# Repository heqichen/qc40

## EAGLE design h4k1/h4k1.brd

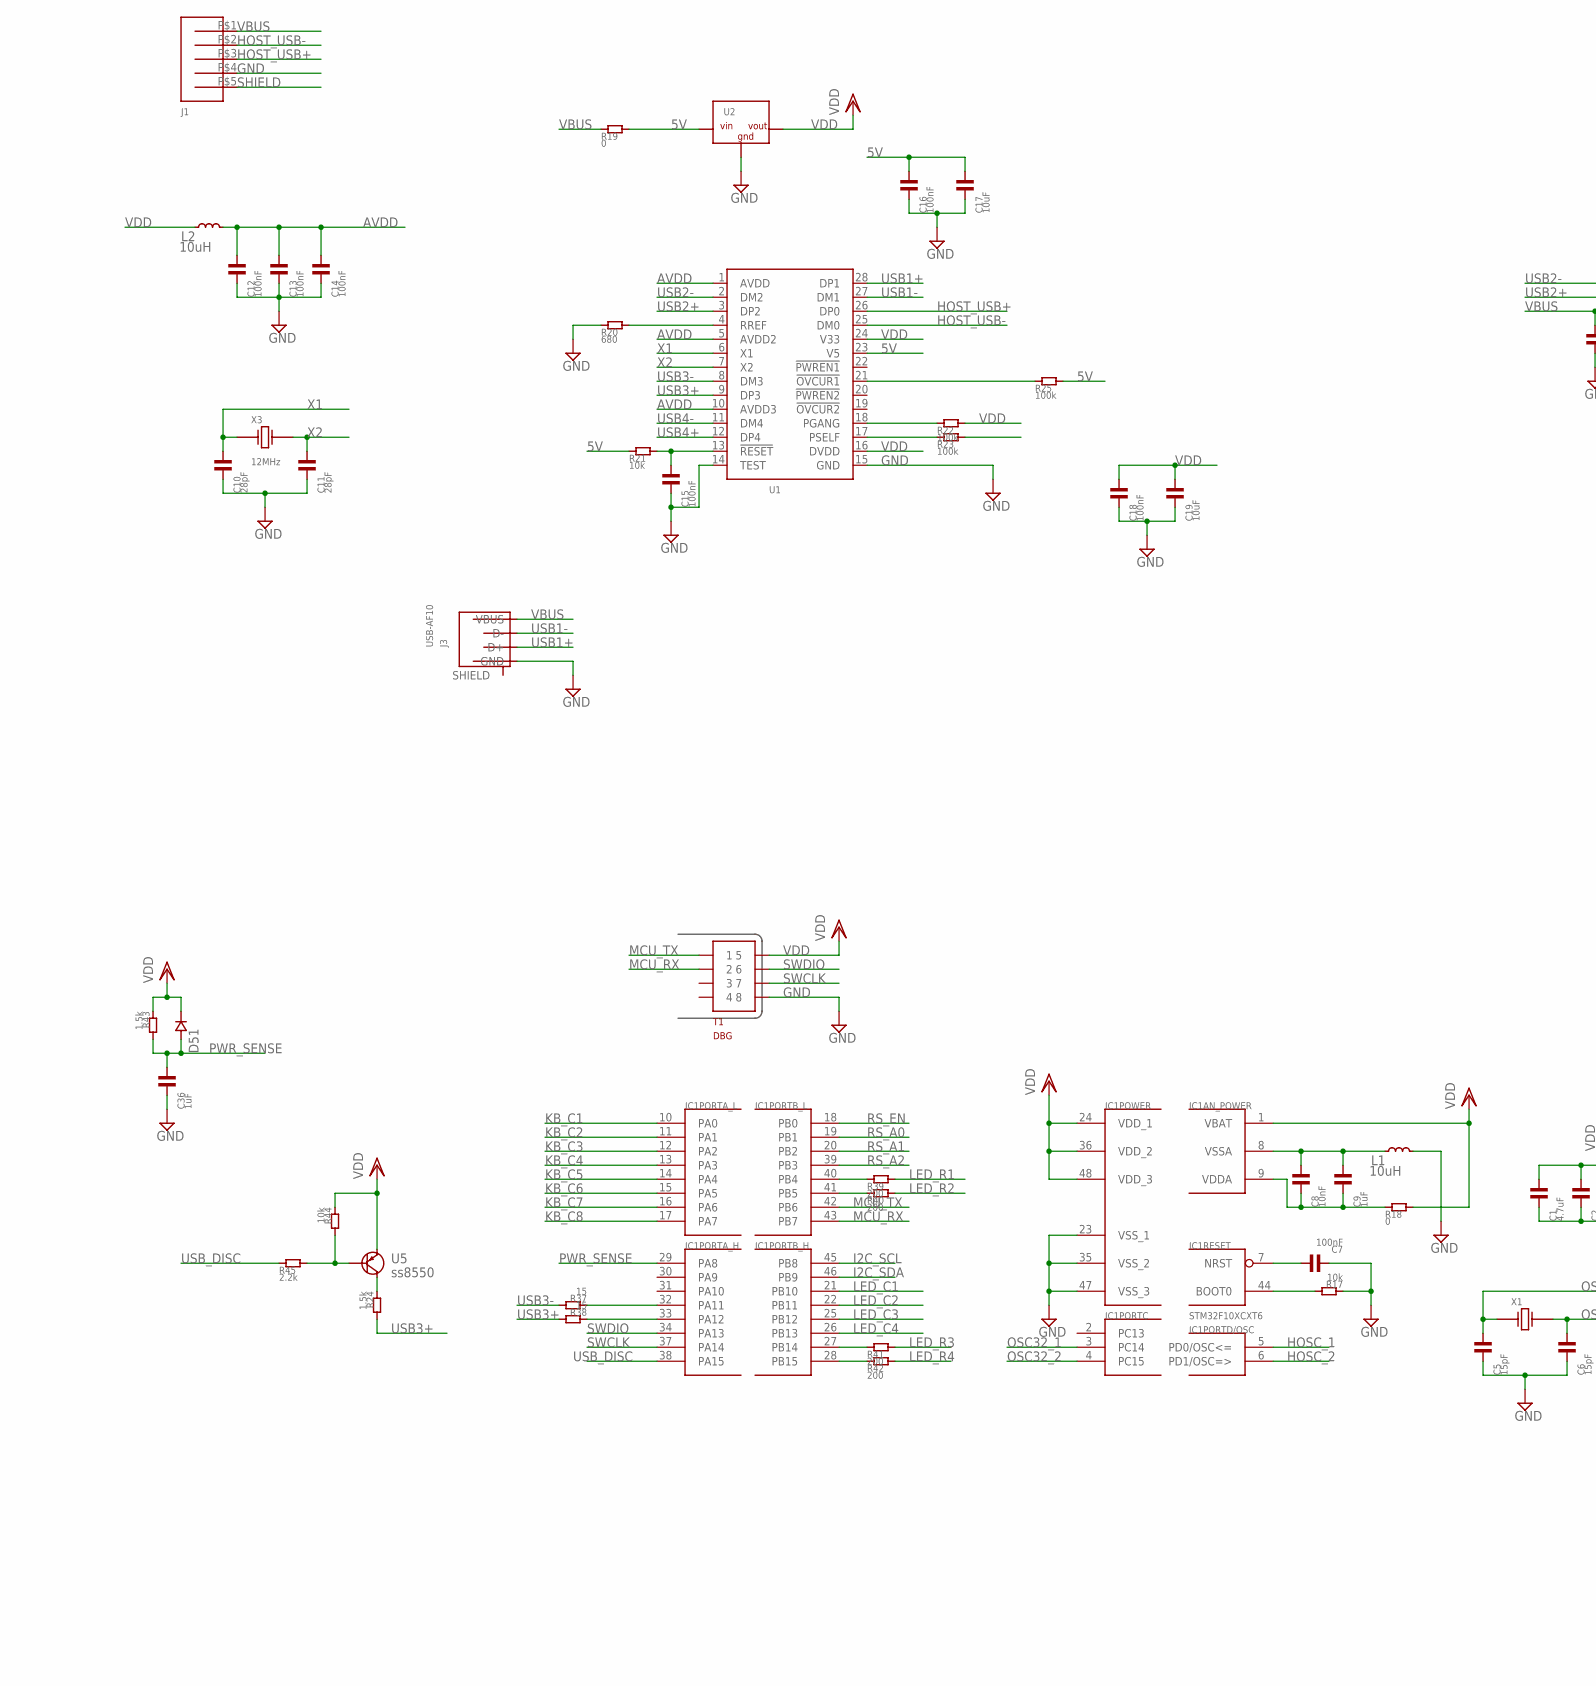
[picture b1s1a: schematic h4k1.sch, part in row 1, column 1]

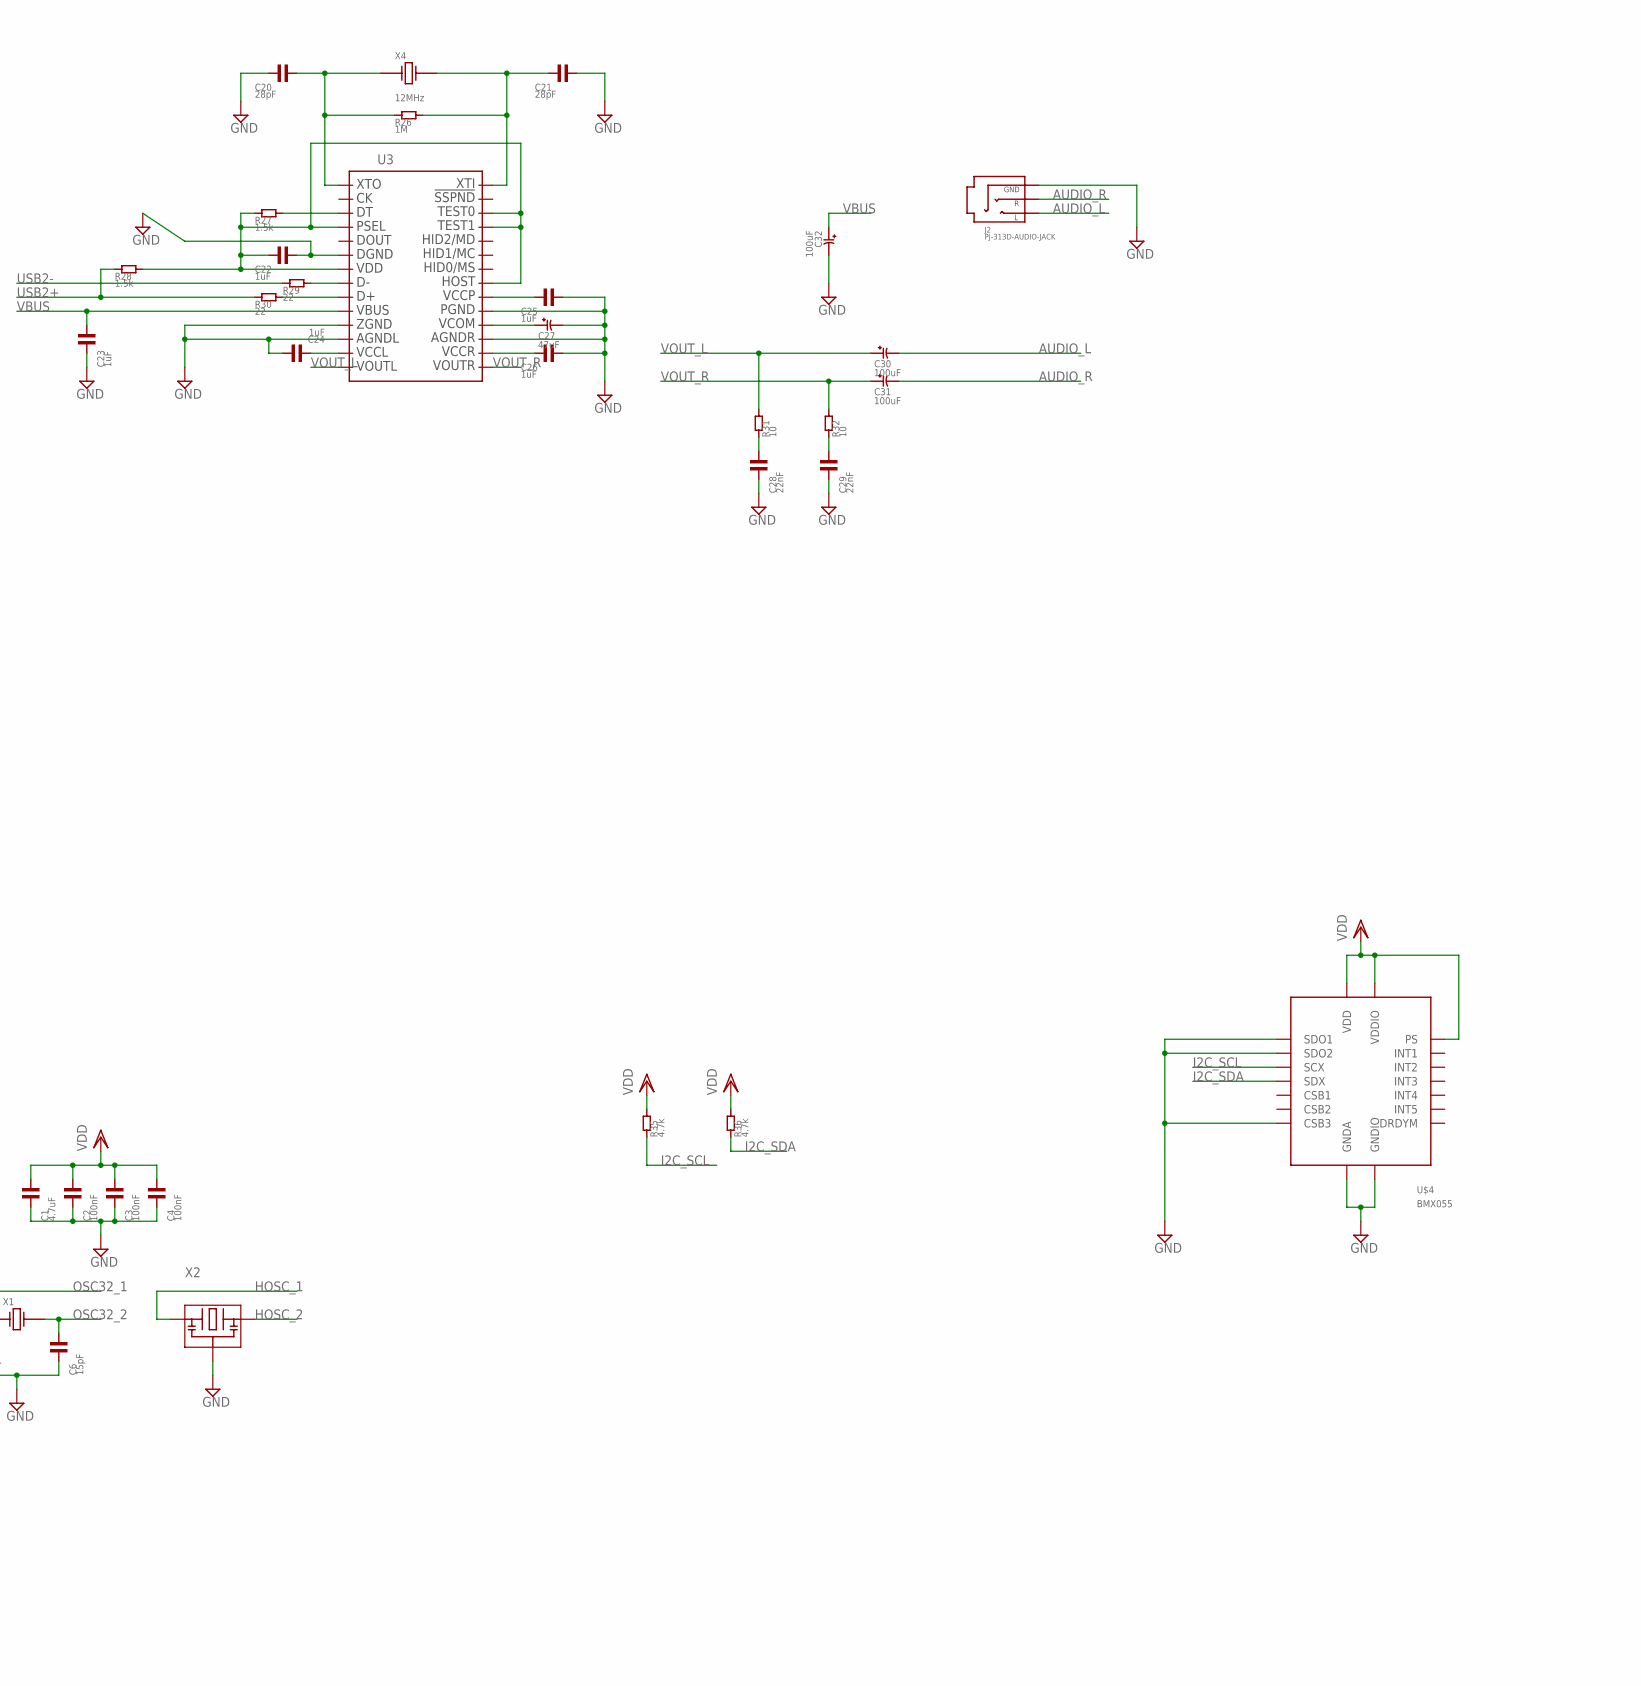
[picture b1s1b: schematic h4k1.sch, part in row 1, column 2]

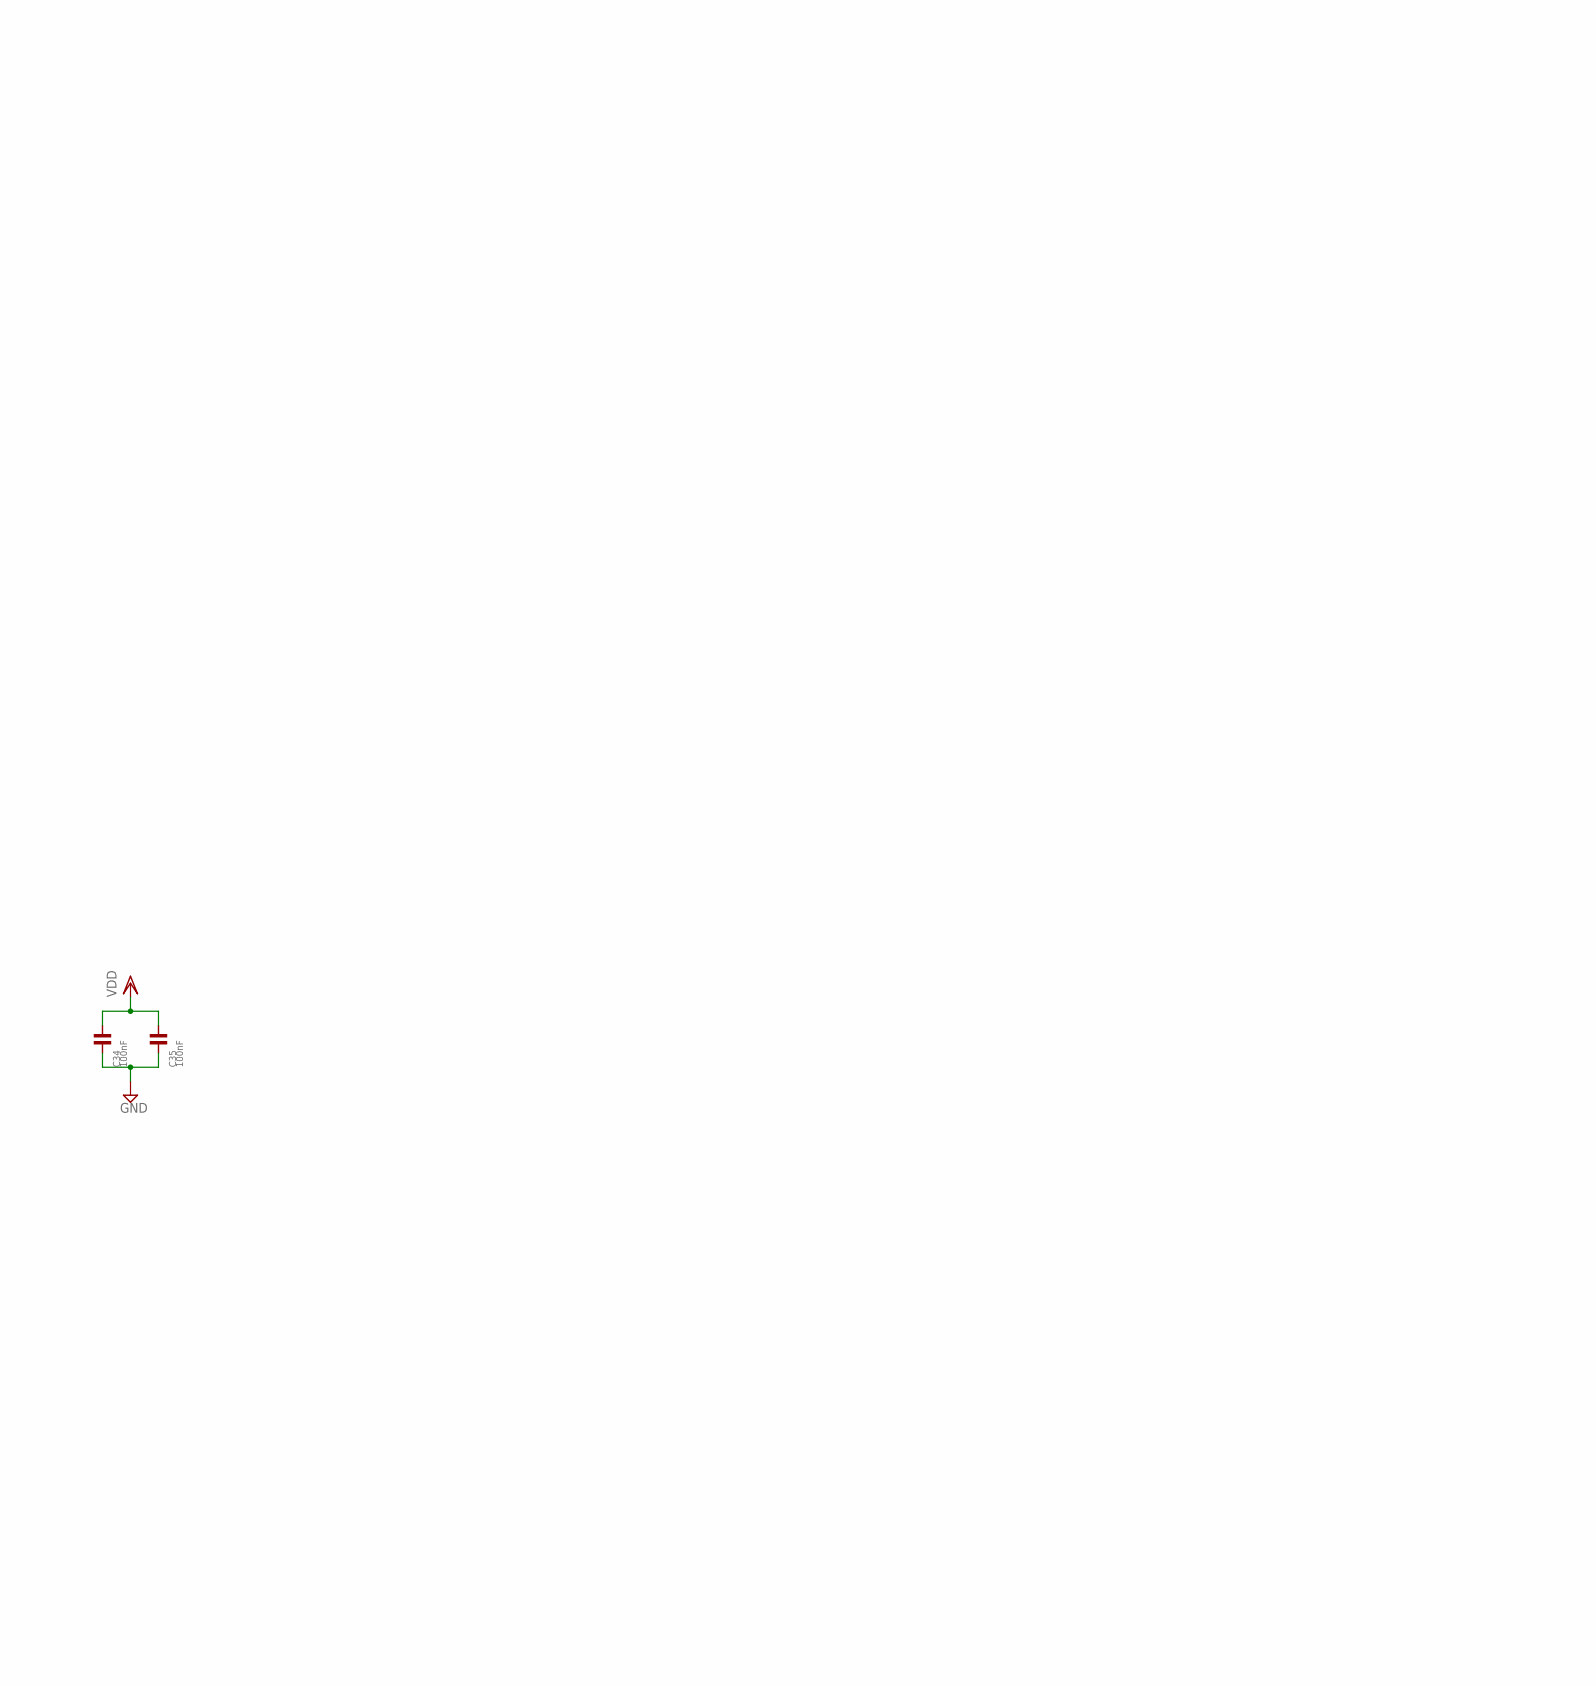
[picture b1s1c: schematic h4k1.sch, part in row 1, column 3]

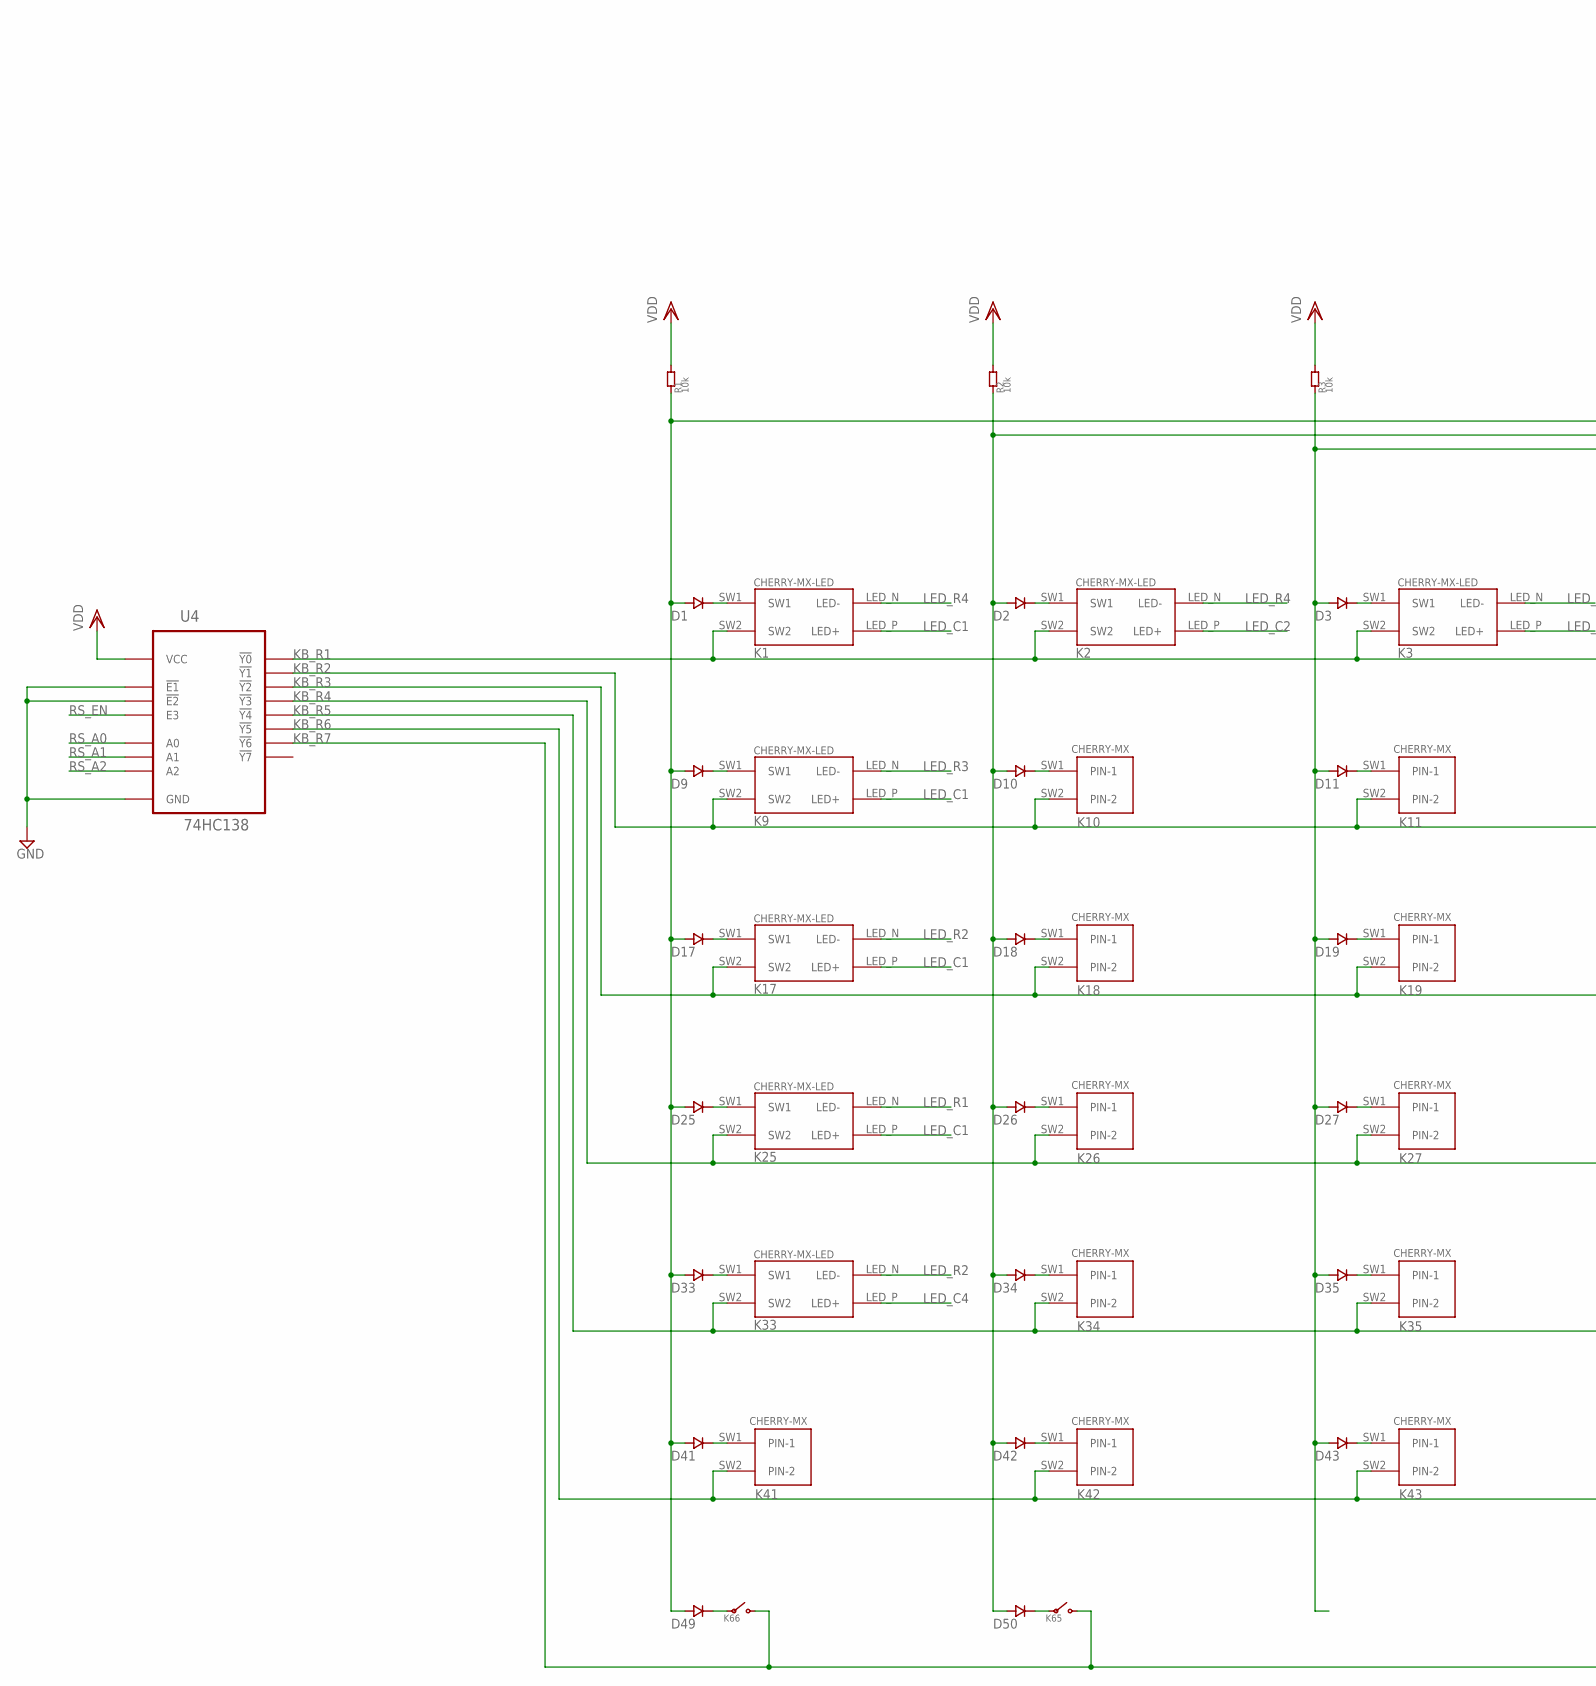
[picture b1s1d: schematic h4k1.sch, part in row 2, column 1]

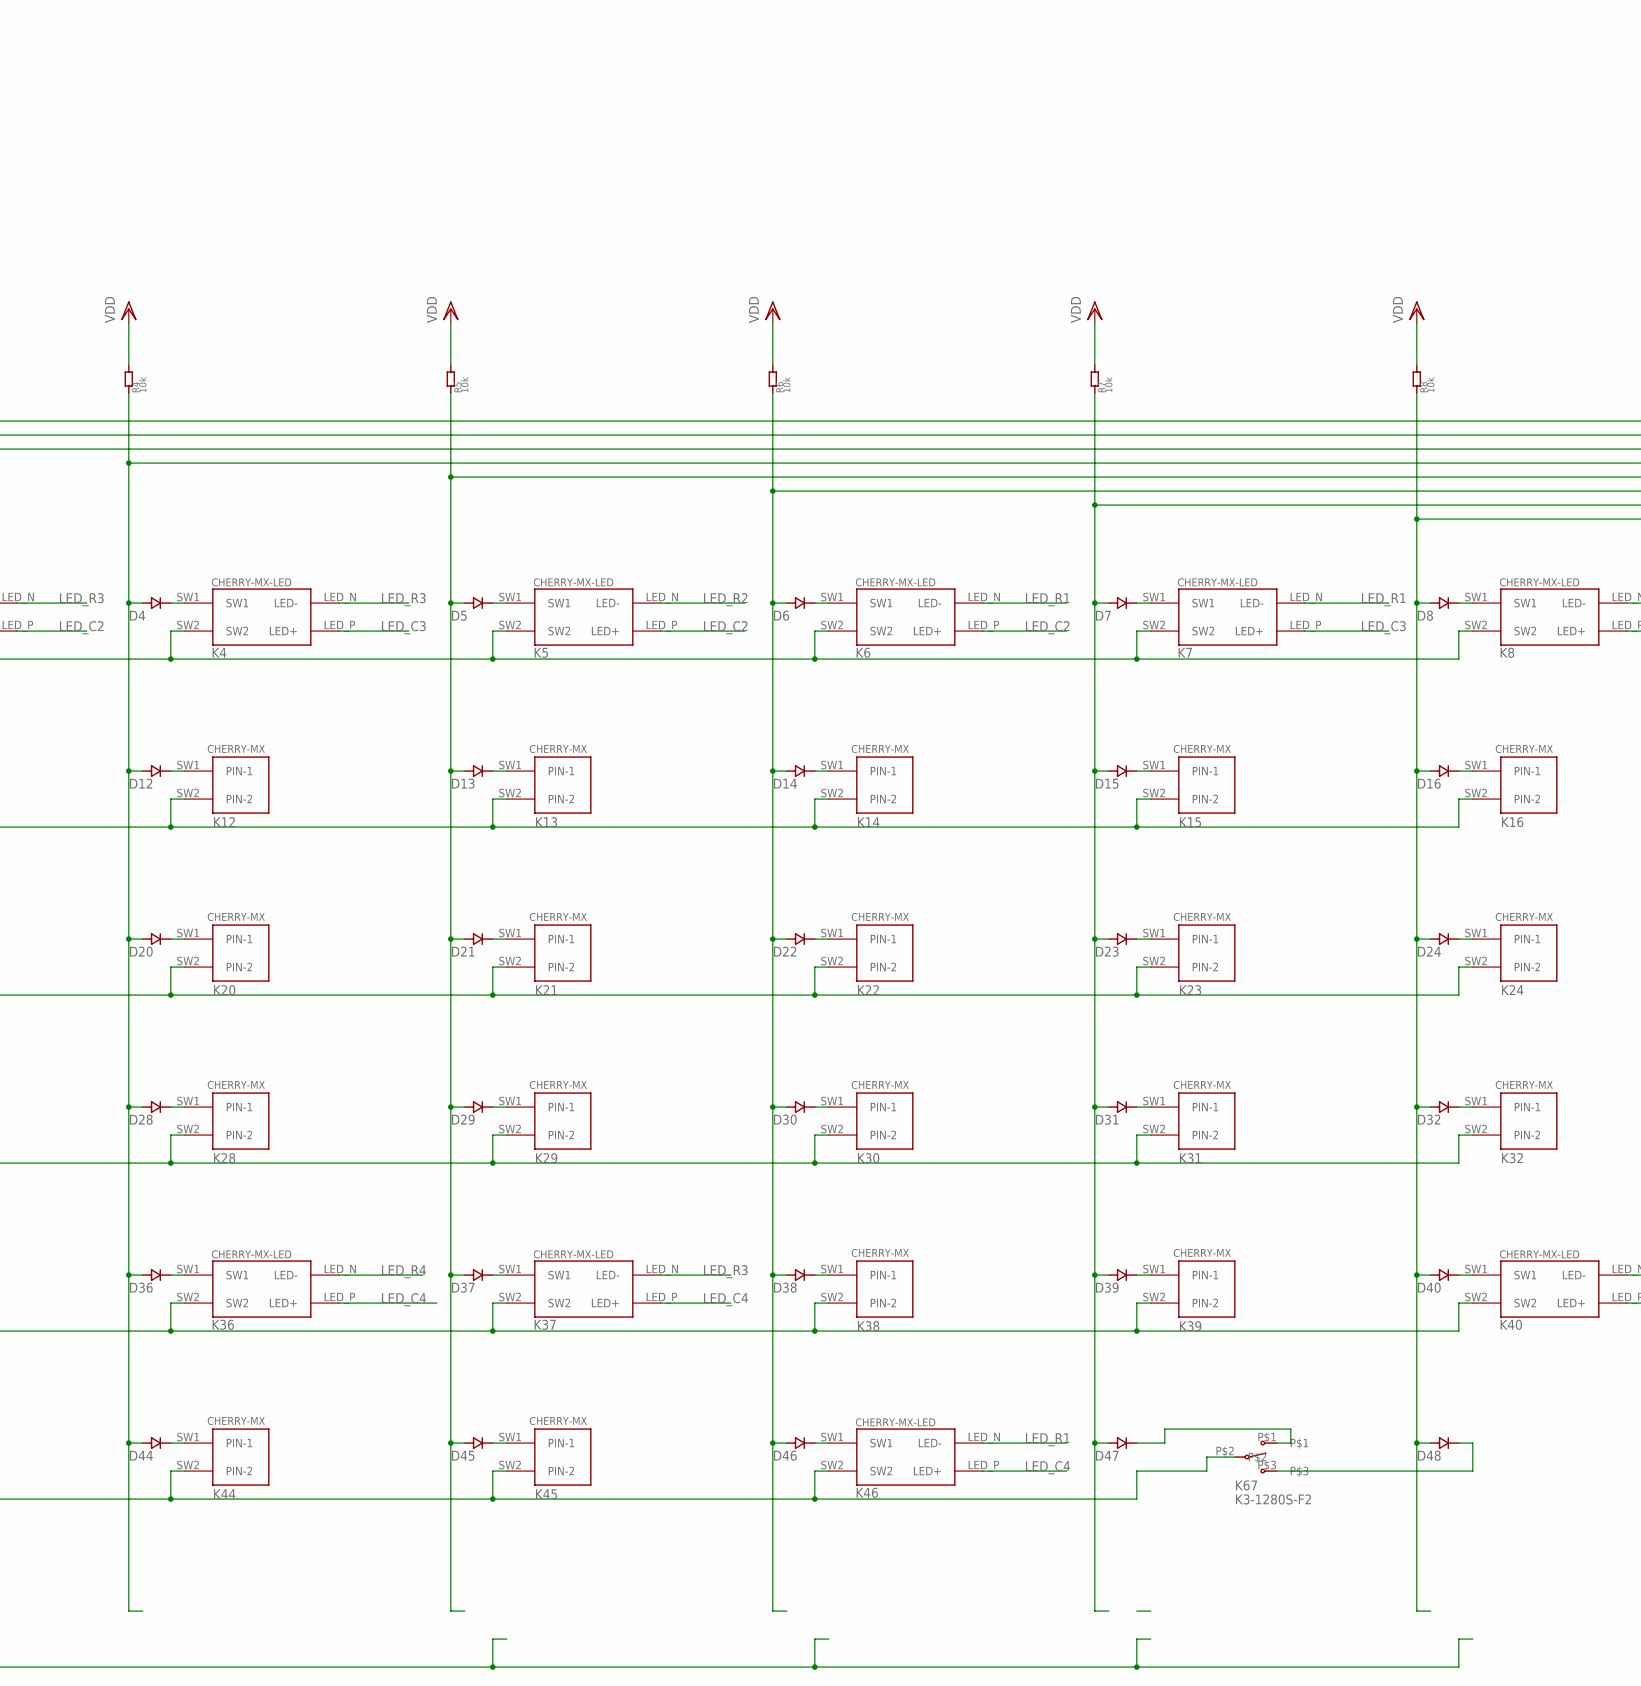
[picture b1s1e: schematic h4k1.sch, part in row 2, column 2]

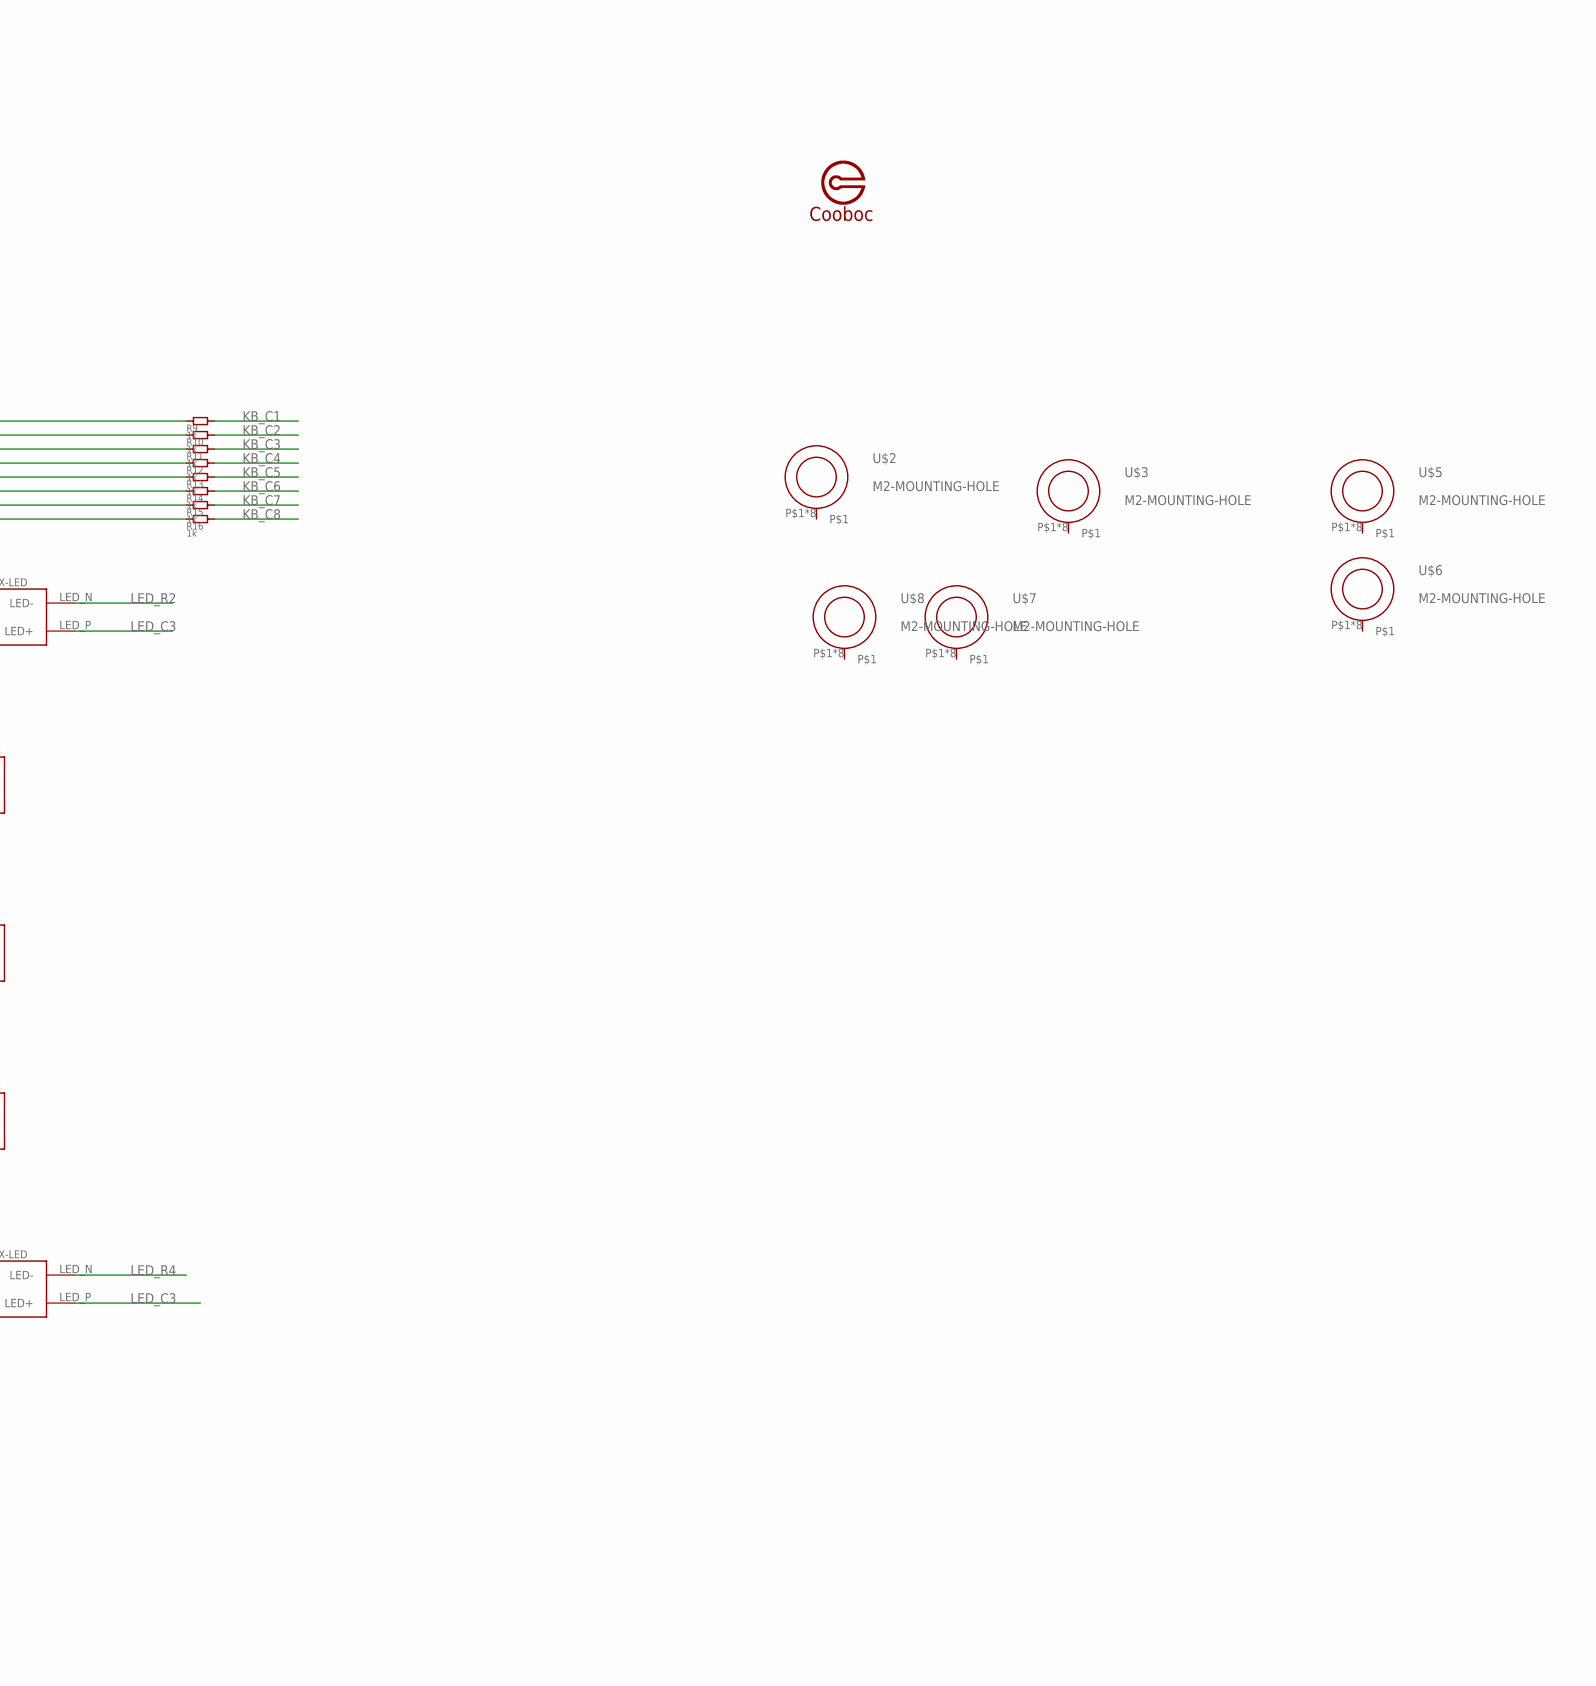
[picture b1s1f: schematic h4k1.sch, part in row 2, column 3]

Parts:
C1: 4.7uF; 0805
C2, C3, C4, C7, C12, C13, C14, C15, C16, C18, C34, C35: 100nF; 0805
C5, C6: 15pF; 0805
C8: 10nF; 0805
C9, C22, C23, C24, C25, C26, C36: 1uF; 0805
C10, C11, C20, C21: 28pF; 0805
C17, C19: 10uF; 0805
C27: 47uF; CPOL-6.3X5.4
C28, C29: 22nF; 0805
C30, C31, C32: 100uF; CPOL-6.3X5.4
D1, D2, D3, D4, D5, D6, D7, D8, D9, D10, D11, D12, D13, D14, D15, D16, D17, D18, D19, D20, D21, D22, D23, D24, D25, D26, D27, D28, D29, D30, D31, D32, D33, D34, D35, D36, D37, D38, D39, D40, D41, D42, D43, D44, D45, D46, D47, D48, D49, D50, D51: IN4148WS-SWITCHING-DIODE; SOD-323
IC1: STM32F10XCXT6; TQFP48
J1: PH-5AWD
J2: PJ-313D-AUDIO-JACK; PJ-313D
J3: USB-AF10
K1, K2, K3, K4, K5, K6, K7, K8, K9, K17, K25, K33, K36, K37, K40, K46: CHERRY-MX-LED
K10, K11, K12, K13, K14, K15, K16, K18, K19, K20, K21, K22, K23, K24, K26, K27, K28, K29, K30, K31, K32, K34, K35, K38, K39, K41, K42, K43, K44, K45: CHERRY-MX
K65, K66: EVQPUL02K; EVQPUL
K67: K3-1280S-F2
L1, L2: 10uH; 0805
R1, R2, R3, R4, R5, R6, R7, R8, R17, R21, R44: 10k; 0805
R9, R10, R11, R12, R13, R14, R15, R16: 1k; 0805
R18, R19: 0; 0805
R20: 680; 0805
R22, R23, R25: 100k; 0805
R24, R27, R28, R43: 1.5k; 0805
R26: 1M; 0805
R29, R30: 22; 0805
R31, R32: 10; 0805
R35, R36: 4.7k; 0805
R37, R38: 15; 0805
R39, R40, R41, R42: 200; 0805
R45: 2.2k; 0805
T1: DBG; CLIP-8P-1.27
U1: GL850G; SSOP28
U2: AMS1117-33; SOT223
U3: PCM2704CDB; SSOP28
U4: 74HC138; SSOP16-208MIL
U5: ss8550; SOT-323
U$1: COOBOC-PLACE
U$2, U$3, U$5, U$6, U$7, U$8: M2-MOUNTING-HOLE
U$4: BMX055
X1: FC-12M-32.768; CRYSTAL-2012
X2: CSTCC8M00G53-R0-7230-8M-15P-RESONATOR; 7230-RESONATOR
X3, X4: 12MHz; 49S

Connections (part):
5V: C16.P$2, C17.P$2, R19.P$2, R21.P$1, R23.P$2, R25.P$2, U1.23 (V5), U2.3 (VIN)
AUDIO_L: C30.P$2, J2.P3, J2.P3@2
AUDIO_R: C31.P$2, J2.P2, J2.P2@2
AVDD: C12.P$2, C13.P$2, C14.P$2, L2.P$2, U1.1 (AVDD), U1.5 (AVDD2), U1.10 (AVDD3)
GND: C1.P$1, C2.P$1, C3.P$1, C4.P$1, C5.P$1, C6.P$1, C7.P$1, C10.P$1, C11.P$1, C12.P$1, C13.P$1, C14.P$1, C15.P$1, C16.P$1, C17.P$1, C18.P$1, C19.P$1, C20.P$1, C21.P$2, C22.P$2, C23.P$1, C24.P$2, C25.P$2, C26.P$2, C27.P$2, C28.P$1, C29.P$1, C32.P$2, C34.P$1, C35.P$1, C36.P$1, IC1.23 (VSS_1), IC1.35 (VSS_2), IC1.47 (VSS_3), J1.P$4, J2.P1, J2.P1@2, J3.P$G (GND), L1.P$2, R17.P$1, R20.P$1, T1.P$8 (8), U1.14 (TEST), U1.15 (GND), U2.1 (GND), U3.6, U3.11, U3.12, U3.17, U3.19, U4.P$4 (!E1), U4.P$5 (!E2), U4.P$8 (GND), U$4.P$4 (GNDA), U$4.P$6 (GNDIO), U$4.P$12 (SDO2), U$4.P$17 (SDO1), U$4.P$20 (CSB3), X2.P$2
HOSC_1: IC1.5 (PD0/OSC<=), X2.P$1
HOSC_2: IC1.6 (PD1/OSC=>), X2.P$3
HOST_USB+: J1.P$3, U1.26 (DP0)
HOST_USB-: J1.P$2, U1.25 (DM0)
I2C_SCL: IC1.45 (PB8), R35.P$1, U$4.P$9 (SCX)
I2C_SDA: IC1.46 (PB9), R36.P$1, U$4.P$11 (SDX)
KB_C1: IC1.10 (PA0), R9.P$2
KB_C2: IC1.11 (PA1), R10.P$2
KB_C3: IC1.12 (PA2), R11.P$2
KB_C4: IC1.13 (PA3), R12.P$2
KB_C5: IC1.14 (PA4), R13.P$2
KB_C6: IC1.15 (PA5), R14.P$2
KB_C7: IC1.16 (PA6), R15.P$2
KB_C8: IC1.17 (PA7), R16.P$2
KB_R1: K1.SW2, K2.SW2, K3.SW2, K4.SW2, K5.SW2, K6.SW2, K7.SW2, K8.SW2, U4.P$15 (!Y0)
KB_R2: K9.SW2, K10.SW2 (PIN-2), K11.SW2 (PIN-2), K12.SW2 (PIN-2), K13.SW2 (PIN-2), K14.SW2 (PIN-2), K15.SW2 (PIN-2), K16.SW2 (PIN-2), U4.P$14 (!Y1)
KB_R3: K17.SW2, K18.SW2 (PIN-2), K19.SW2 (PIN-2), K20.SW2 (PIN-2), K21.SW2 (PIN-2), K22.SW2 (PIN-2), K23.SW2 (PIN-2), K24.SW2 (PIN-2), U4.P$13 (!Y2)
KB_R4: K25.SW2, K26.SW2 (PIN-2), K27.SW2 (PIN-2), K28.SW2 (PIN-2), K29.SW2 (PIN-2), K30.SW2 (PIN-2), K31.SW2 (PIN-2), K32.SW2 (PIN-2), U4.P$12 (!Y3)
KB_R5: K33.SW2, K34.SW2 (PIN-2), K35.SW2 (PIN-2), K36.SW2, K37.SW2, K38.SW2 (PIN-2), K39.SW2 (PIN-2), K40.SW2, U4.P$11 (!Y4)
KB_R6: K41.SW2 (PIN-2), K42.SW2 (PIN-2), K43.SW2 (PIN-2), K44.SW2 (PIN-2), K45.SW2 (PIN-2), K46.SW2, K67.P$2, U4.P$10 (!Y5)
KB_R7: K65.P$2, K65.P$4, K66.P$2, K66.P$4, U4.P$9 (!Y6)
LED_C1: IC1.21 (PB10), K1.LED_P (LED+), K9.LED_P (LED+), K17.LED_P (LED+), K25.LED_P (LED+)
LED_C2: IC1.22 (PB11), K2.LED_P (LED+), K3.LED_P (LED+), K5.LED_P (LED+), K6.LED_P (LED+)
LED_C3: IC1.25 (PB12), K4.LED_P (LED+), K7.LED_P (LED+), K8.LED_P (LED+), K40.LED_P (LED+)
LED_C4: IC1.26 (PB13), K33.LED_P (LED+), K36.LED_P (LED+), K37.LED_P (LED+), K46.LED_P (LED+)
LED_R1: K6.LED_N (LED-), K7.LED_N (LED-), K25.LED_N (LED-), K46.LED_N (LED-), R39.P$2
LED_R2: K5.LED_N (LED-), K8.LED_N (LED-), K17.LED_N (LED-), K33.LED_N (LED-), R40.P$2
LED_R3: K3.LED_N (LED-), K4.LED_N (LED-), K9.LED_N (LED-), K37.LED_N (LED-), R41.P$2
LED_R4: K1.LED_N (LED-), K2.LED_N (LED-), K36.LED_N (LED-), K40.LED_N (LED-), R42.P$2
MCU_RX: IC1.43 (PB7), T1.P$2 (2)
MCU_TX: IC1.42 (PB6), T1.P$1 (1)
unnamed: D1.P$2, K1.SW1
unnamed: D1.P$1, D9.P$1, D17.P$1, D25.P$1, D33.P$1, D41.P$1, D49.P$1, R1.P$1, R9.P$1
unnamed: D9.P$2, K9.SW1
unnamed: D2.P$2, K2.SW1
unnamed: D2.P$1, D10.P$1, D18.P$1, D26.P$1, D34.P$1, D42.P$1, D50.P$1, R2.P$1, R10.P$1
unnamed: IC1.44 (BOOT0), R17.P$2
unnamed: D3.P$2, K3.SW1
unnamed: C8.P$2, C9.P$2, IC1.8 (VSSA), L1.P$1
unnamed: C7.P$2, IC1.7 (NRST)
unnamed: D4.P$2, K4.SW1
unnamed: D4.P$1, D12.P$1, D20.P$1, D28.P$1, D36.P$1, D44.P$1, R4.P$1, R12.P$1
unnamed: D5.P$2, K5.SW1
unnamed: D5.P$1, D13.P$1, D21.P$1, D29.P$1, D37.P$1, D45.P$1, R5.P$1, R13.P$1
unnamed: D6.P$2, K6.SW1
unnamed: D6.P$1, D14.P$1, D22.P$1, D30.P$1, D38.P$1, D46.P$1, R6.P$1, R14.P$1
unnamed: D7.P$2, K7.SW1
unnamed: D7.P$1, D15.P$1, D23.P$1, D31.P$1, D39.P$1, D47.P$1, R7.P$1, R15.P$1
unnamed: D10.P$2, K10.SW1 (PIN-1)
unnamed: D8.P$2, K8.SW1
unnamed: D8.P$1, D16.P$1, D24.P$1, D32.P$1, D40.P$1, D48.P$1, R8.P$1, R16.P$1
unnamed: C8.P$1, C9.P$1, IC1.9 (VDDA), R18.P$1
unnamed: D11.P$2, K11.SW1 (PIN-1)
unnamed: D3.P$1, D11.P$1, D19.P$1, D27.P$1, D35.P$1, D43.P$1, R3.P$1, R11.P$1
unnamed: C15.P$2, R21.P$2, U1.13 (!RESET)
unnamed: D12.P$2, K12.SW1 (PIN-1)
unnamed: R20.P$2, U1.4 (RREF)
unnamed: D13.P$2, K13.SW1 (PIN-1)
unnamed: R22.P$1, U1.18 (PGANG)
unnamed: D14.P$2, K14.SW1 (PIN-1)
unnamed: R23.P$1, U1.17 (PSELF)
unnamed: D15.P$2, K15.SW1 (PIN-1)
unnamed: C20.P$2, R26.P$1, U3.1, X4.P$1
unnamed: D16.P$2, K16.SW1 (PIN-1)
unnamed: R25.P$1, U1.21 (!OVCUR1)
unnamed: D17.P$2, K17.SW1
unnamed: C21.P$1, R26.P$2, U3.28, X4.P$2
unnamed: D18.P$2, K18.SW1 (PIN-1)
unnamed: R29.P$2, U3.8
unnamed: D19.P$2, K19.SW1 (PIN-1)
unnamed: R30.P$2, U3.9
unnamed: D20.P$2, K20.SW1 (PIN-1)
unnamed: C22.P$1, R27.P$1, R28.P$2, U3.4, U3.7, U3.21, U3.25, U3.26
unnamed: D21.P$2, K21.SW1 (PIN-1)
unnamed: C25.P$1, U3.20
unnamed: D22.P$2, K22.SW1 (PIN-1)
unnamed: D23.P$2, K23.SW1 (PIN-1)
unnamed: C24.P$1, U3.13
unnamed: D24.P$2, K24.SW1 (PIN-1)
unnamed: R27.P$2, U3.3
unnamed: D25.P$2, K25.SW1
unnamed: D26.P$2, K26.SW1 (PIN-1)
unnamed: D27.P$2, K27.SW1 (PIN-1)
unnamed: C26.P$1, U3.16
unnamed: C27.P$1, U3.18
unnamed: D28.P$2, K28.SW1 (PIN-1)
unnamed: D29.P$2, K29.SW1 (PIN-1)
unnamed: D30.P$2, K30.SW1 (PIN-1)
unnamed: D31.P$2, K31.SW1 (PIN-1)
unnamed: D32.P$2, K32.SW1 (PIN-1)
unnamed: D33.P$2, K33.SW1
unnamed: D34.P$2, K34.SW1 (PIN-1)
unnamed: C29.P$2, R32.P$1
unnamed: D35.P$2, K35.SW1 (PIN-1)
unnamed: C28.P$2, R31.P$1
unnamed: D36.P$2, K36.SW1
unnamed: D47.P$2, K67.P$1
unnamed: D37.P$2, K37.SW1
unnamed: D49.P$2, K66.P$1, K66.P$3
unnamed: D38.P$2, K38.SW1 (PIN-1)
unnamed: IC1.32 (PA11), R37.P$1
unnamed: D39.P$2, K39.SW1 (PIN-1)
unnamed: IC1.33 (PA12), R38.P$1
unnamed: D40.P$2, K40.SW1
unnamed: IC1.40 (PB4), R39.P$1
unnamed: D41.P$2, K41.SW1 (PIN-1)
unnamed: D42.P$2, K42.SW1 (PIN-1)
unnamed: D43.P$2, K43.SW1 (PIN-1)
unnamed: IC1.41 (PB5), R40.P$1
unnamed: IC1.28 (PB15), R42.P$1
unnamed: D44.P$2, K44.SW1 (PIN-1)
unnamed: D45.P$2, K45.SW1 (PIN-1)
unnamed: D46.P$2, K46.SW1
unnamed: IC1.27 (PB14), R41.P$1
unnamed: D48.P$2, K67.P$3
unnamed: R44.P$2, R45.P$2, U5.P$1 (P$B)
unnamed: D50.P$2, K65.P$1, K65.P$3
unnamed: R24.P$1, U5.P$3 (P$C)
OSC32_1: C5.P$2, IC1.3 (PC14), X1.P$1
OSC32_2: C6.P$2, IC1.4 (PC15), X1.P$2
PWR_SENSE: C36.P$2, D51.P$1, IC1.29 (PA8), R43.P$2
RS_A0: IC1.19 (PB1), U4.P$1 (A0)
RS_A1: IC1.20 (PB2), U4.P$2 (A1)
RS_A2: IC1.39 (PB3), U4.P$3 (A2)
RS_EN: IC1.18 (PB0), U4.P$6 (E3)
SHIELD: J1.P$5
SWCLK: IC1.37 (PA14), T1.P$7 (7)
SWDIO: IC1.34 (PA13), T1.P$6 (6)
USB1+: J3.P$D+ (D+), U1.28 (DP1)
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
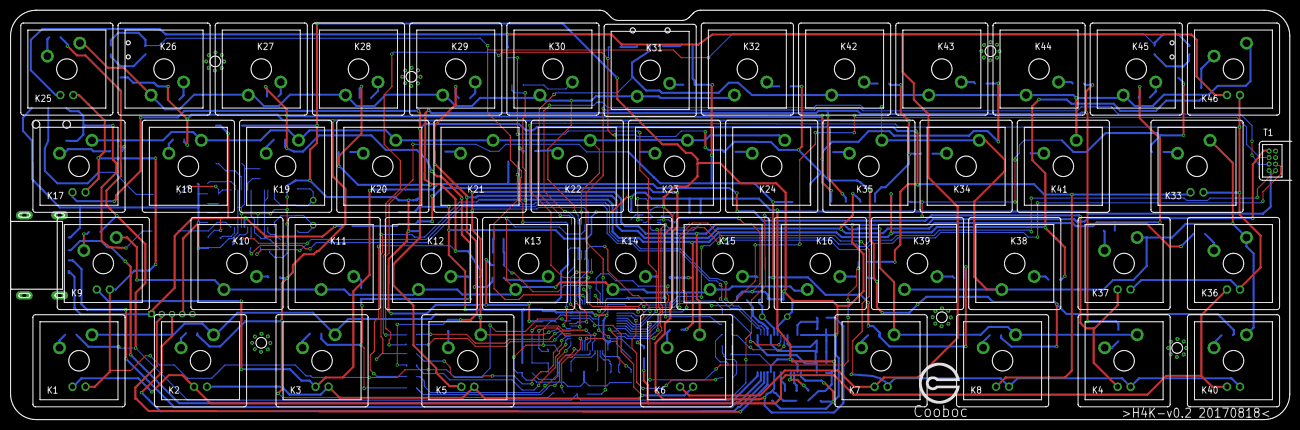
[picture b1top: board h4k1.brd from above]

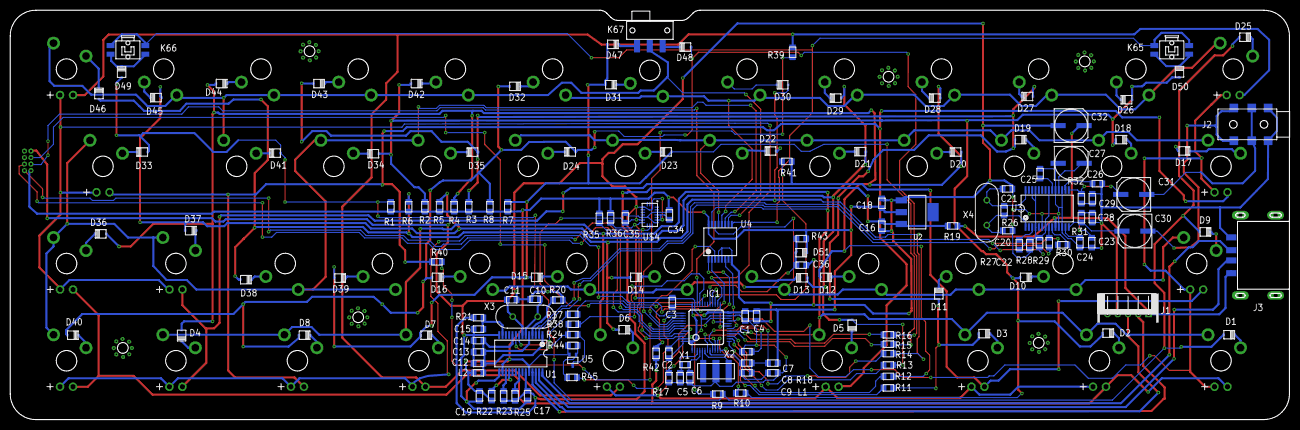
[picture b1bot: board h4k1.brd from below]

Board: 2 copper layers, 250.0 x 80.0 mm, 202 parts (148 on the bottom side), 145 nets.

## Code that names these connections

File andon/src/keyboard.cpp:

#include "keyboard.h"

#include <gpio.h>
#include <hardware_serial.h>
#include <cooboc.h>

#define PIN_KB_EN	B0
#define PIN_KB_A0	B1
#define PIN_KB_A1	B2
#define PIN_KB_A2	B3

#define PIN_KB_C1	A0
#define PIN_KB_C2	A1
#define PIN_KB_C3	A2
#define PIN_KB_C4	A3
#define PIN_KB_C5	A4
#define PIN_KB_C6	A5
#define PIN_KB_C7	A6
#define PIN_KB_C8	A7


uint8_t PIN_KB_COLS[] = {PIN_KB_C1, PIN_KB_C2, PIN_KB_C3, PIN_KB_C4, PIN_KB_C5, PIN_KB_C6, PIN_KB_C7, PIN_KB_C8};

void Keyboard::setup(EventLoop *el)
{
	int i;
	mEventLoop = el;
	for (i=0; i<8; ++i)
	{
		pinMode(PIN_KB_COLS[i], INPUT);
	}


	pinMode(PIN_KB_EN, OUTPUT);
	pinMode(PIN_KB_A0, OUTPUT);
	pinMode(PIN_KB_A1, OUTPUT);
	pinMode(PIN_KB_A2, OUTPUT);

	digitalWrite(PIN_KB_EN, LOW);
	digitalWrite(PIN_KB_A0, LOW);
	digitalWrite(PIN_KB_A1, LOW);
	digitalWrite(PIN_KB_A2, LOW);

	mLastTickTime = 0;
	for (i=0; i<56; ++i)
	{
		mKeys[i].setup();
	}
}

void Keyboard::tick()
{
	if (millis() - mLastTickTime > 1)
	{
		mLastTickTime = millis();
		int x, y;
		digitalWrite(PIN_KB_EN, HIGH);
		for (y=0; y<7; ++y)
		{
			digitalWrite(PIN_KB_A0, (y&0x01)>0?HIGH:LOW);
			digitalWrite(PIN_KB_A1, ((y>>1)&0x01)>0?HIGH:LOW);
			digitalWrite(PIN_KB_A2, ((y>>2)&0x01)>0?HIGH:LOW);
			
			for(x=0; x<8; ++x)
			{
				mKeys[y*8 + x].tick(digitalRead(PIN_KB_COLS[x]));
				if (mKeys[y*8 + x].hasChanged())
				{
					if (mKeys[y*8+x].getNewValue() > 0)
					{
						mEventLoop->newEvent(EVENT_KEY_UP, y*8 + x);
					}
					else
					{
						mEventLoop->newEvent(EVENT_KEY_DOWN, y*8 + x);
					}
					
					/*
					Serial.print("Key: ");
					Serial.print(y*8+x);
					Serial.print(" has changed to ");
					Serial.println(mKeys[y*8+x].getNewValue());
					*/
				}
				//Serial.print(digitalRead(PIN_KB_COLS[x]));
			}
			//Serial.println("");
		}
		//Serial.println("");
	}
}
